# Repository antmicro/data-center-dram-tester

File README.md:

# Data Center RDIMM DDR4 Tester

Copyright (c) 2021-2023 [Antmicro](https://antmicro.com)

## Overview

This repository contains open hardware KiCad design files for an experimental platform built around the Xilinx Kintex-7 FPGA which can be used to interface with RDIMM DDR4 RAM modules used in data centers.

This hardware platform is used in Antmicro's and Google's [Rowhammer testing framework](https://github.com/antmicro/litex-rowhammer-tester) which can be used to perform (and potentially mitigate) Rowhammer attacks on DRAM memories. You can learn more about Rowhammer and our work towards mitigating it in a Google Open Source blog note [describing a related platform](https://opensource.googleblog.com/2021/11/Open%20source%20DDR%20controller%20framework%20for%20mitigating%20Rowhammer.html).
The usage instructions for this board are also provided in the [Rowhammer testing framework documentation](https://litex-rowhammer-tester.readthedocs.io/en/latest/). 

## Repository structure

The main repository directory contains KiCad PCB project files, a LICENSE and README.
The remaining files are stored in the following directories:

* `lib` - contains the component libraries
* `img` - contains graphics for this README

## Key Features

* Kintex-7 FPGA (XC7K160T-FFG676)
* DDR4 RDIMM connector with hotswap
* HDMI output connector
* Ethernet RJ45 connector with 1GbE transciever
* USB-C debug connector with FT4232HQ FTDI USB controller
* JTAG
* microSD card slot
* 16 MBytes S25FL128S QSPI FLASH memory
* S27KL0641 HyperRAM
* External 7-12V DC power input
* PoE++
* Power consumption monitoring
* 5 user LEDs
* Optional FMC HPC expansion connector

## Block diagram

## License

This project is published under the [Apache-2.0](LICENSE) license.

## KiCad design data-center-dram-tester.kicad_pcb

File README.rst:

=======================
Data Center DRAM Tester
=======================

Copyright (c) 2021-2022 `Antmicro <https://www.antmicro.com>`_

.. figure:: img/data-center-dram-tester.png

Overview
--------

This repository contains open hardware design files for an experimental platform built around Xilinx Kintex-7 FPGA.
The main purpose of this platform is to develop and customize RAM controllers supporting RDIMM DDR4 RAM modules used in data centers.

This hardware platform is supported by the `LiteX Rowhammer Tester <https://github.com/antmicro/litex-rowhammer-tester>`_ gateware. It can be used to investigate Rowhammer DRAM attacks. You can learn more about Rowhammer attacks from this blog `note <https://antmicro.com/blog/2021/08/open-source-ddr-test-framework-for-rowhammer/>`_.
The usage instructions for this board are also provided in the `LiteX Row Hammer Tester documentation <https://litex-rowhammer-tester.readthedocs.io/en/latest/>`_. 

The design files were prepared in KiCad.

Repository structure
--------------------
The main repository directory contains KiCad PCB project files, a LICENSE and README.
The remaining files are stored in the following directories:

* ``lib`` - contains the component libraries
* ``img`` - contains graphics for this README

Key Features
------------

* Kintex-7 FPGA - XC7K100T-FBG686
* DDR4 RDIMM connector
* HDMI output connector
* Ethernet RJ45 connector with 1GbE transciever
* Micro USB debug connector with FT4232HQ FTDI USB controller
* JTAG
* microSD card slot
* 16Mbytes S25FL128S QSPI FLASH memory
* S27KL0641 HyperRAM
* External 7-12V power input
* 5 user LEDs
* 4 user buttons

License
=======

`Apache-2.0 <LICENSE>`_

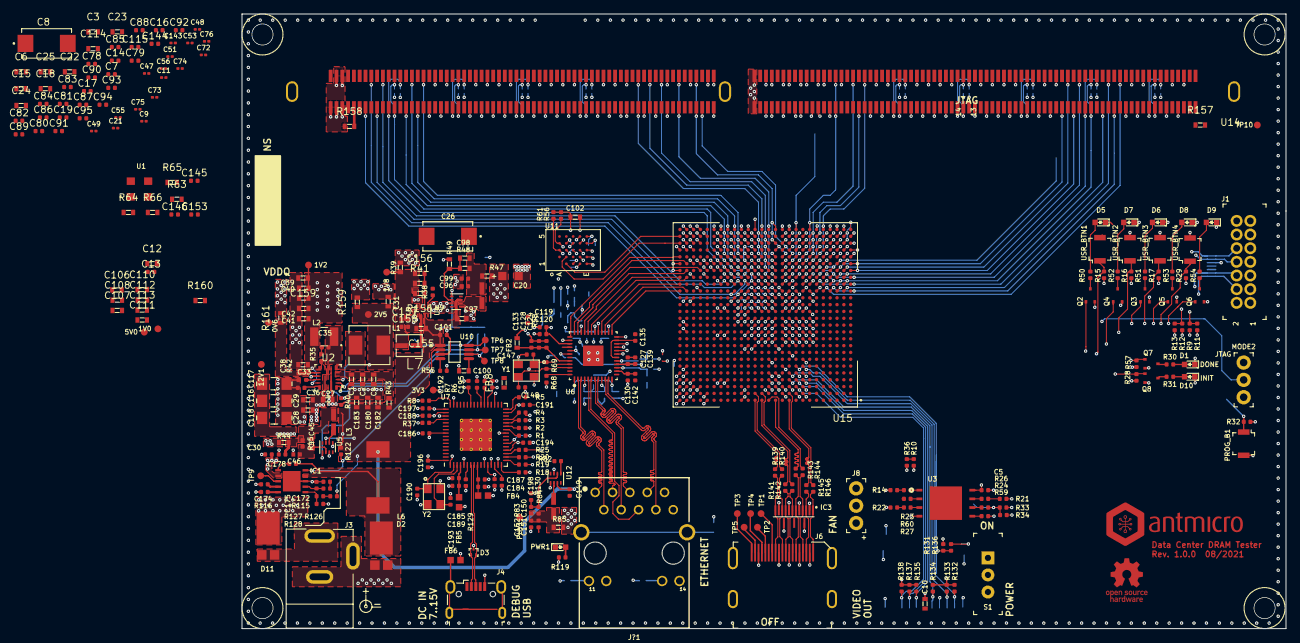
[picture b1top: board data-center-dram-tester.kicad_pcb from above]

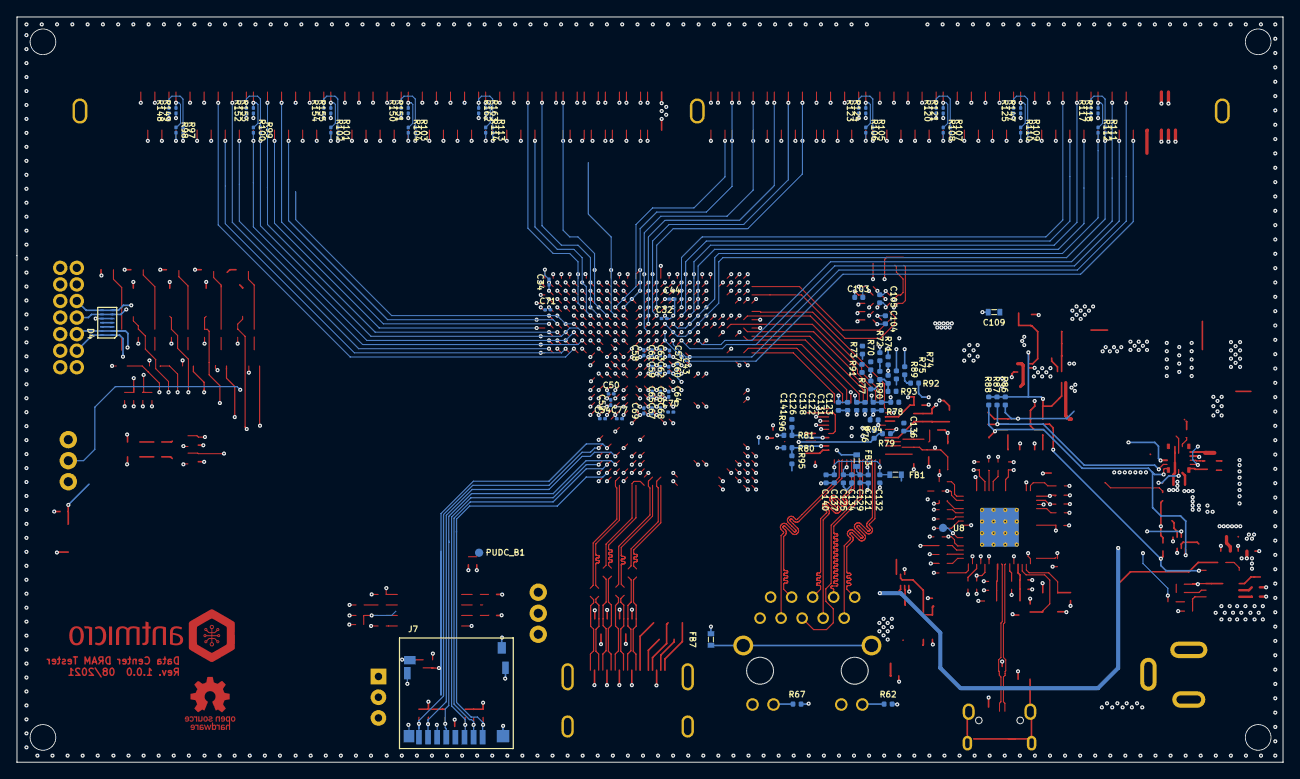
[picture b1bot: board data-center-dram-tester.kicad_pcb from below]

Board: 10 copper layers, 152.9 x 90.0 mm, 430 parts (109 on the bottom side), 375 nets.

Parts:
0V6, 1V0, 1V2, 1V8, 2V5, 3V3, 5V0, 12V1: TP_SMD1MM; Testpoint_smd_1mm
C1, C33, C155: C_10u_0603; 0603-cap
C2: C_100n_0603; 0603-cap
C3, C6, C12, C15, C18, C22, C23, C24, C25, C102, C114, C180, C182, C183: C_47u_0603; 0603-cap
C4, C10: C_1u_0603; 0603-cap
C5, C35, C101, C103, C104, C105, C145, C146, C153, C178, C184, C185, C186, C188, C191, C192, C194, C196, C197, C198: C_100n_0402_6V3; 0402-cap
C7, C14, C16, C17, C19, C78, C79, C80, C81, C82, C83, C84, C85, C86, C87, C88, C89, C90, C91, C92, C93, C94, C95, C115, C119, C121, C123, C124, C132, C144, C187, C189, C195: C_4u7_0402; 0402-cap
C8, C26: C_330u_KEMET_D; KEMET_D
C9, C11, C21, C32, C34, C43, C44, C47, C48, C49, C50, C51, C52, C53, C54, C55, C56, C57, C58, C59, C60, C61, C62, C63, C64, C65, C66, C67, C68, C69, C70, C71, C72, C73, C74, C75, C76, C77, C143: C_100n_0201; 0201-res
C13, C36, C120, C122, C125, C126, C127: C_470n_0402; 0402-cap
C20: C_100u_KEMET_A; KEMET_A
C27, C28, C29: C_10u_25V_0603; 0603-cap
C30: C_100n_0402_16V; 0402-cap
C31, C39, C40, C41, C42, C159: C_22u_0603; 0603-cap
C38, C46, C96, C99, C149, C151, C152, C157, C158: C_10u_0402; 0402-cap
C45, C98, C156: C_120p_0603; 0603-cap
C97: C_4u7_0603; 0603-cap
C100, C106, C107, C108, C109, C110, C111, C112, C113: C_10n_0603; 0603-cap
C116, C117, C118: C_47u_16V_1206; 1206-cap
C128: C_100n_0402; 0402-cap
C129, C130, C131, C133, C134, C135, C136, C137, C138, C139, C140, C141, C142, C174: C_10n_0402; 0402-cap
C147, C148: C_22p_0402; 0402-cap
C150: C_120p_0402; 0402-cap
C172: C_4n7_0402; 0402-cap
C175: C_47p_0402; 0402-cap
C190, C193: C_18p_0402; 0402-cap
D1, D5, D6, D7, D8, D9, D10: KP-1608CGCK; LED_0603
D2, D11: PDS760-13
D3: TPD2E009; SOT-3
D4: TPD6E05U06
FB1, FB2, FB3, FB7, FB8: BLM18PG121SN1D; 0603-res
FB4, FB5, FB6: BLM18AG601SN1D; 0603
IC1: TPS54561; WSON-10_4x4
IC3: TPD8S009DSMR; R-PDSO-N15
J1: 0878311420; PinHeader_2x7_P2mm_Drill1mm
J3: DC_SOCKET
J4: WE_629105150521; USB_Micro_B_Female_629105150521
J6: 685119134923; HDMI_A_Female_685119134923
J7: 1140084168; MicroSD_1140084168
J8: 61300311121; PinHeader_1x3_P2.54_Drill1.1mm
J?1: WE-RJ45_7499111121A; 7499111121A
L1: IHLP2020BZER4R7M01
L2: DFE322512F-R68M=P2; INDC3225X120N
L3, L4, L5, L7: IHLP1212AEERR47M11; IHLP-1212AE
L6: WE_7447798720
MODE2: 61300311121; PinHeader_1x3_P2.54_Drill1.1mm
N1: oshw_logo; oshw-logo
N2: antmicro_logo; antmicro-logo_scaled_20mm
PHY1: TP_SMD1MM; Testpoint_smd_1mm
PROG_B1: B3U-1000P; Switch_Tactile_SMD_B3U-1000P
PUDC_B1: test; Testpoint_smd_1mm
PWR1: KP-1608CGCK; LED_0603
Q2, Q3, Q4, Q5, Q6, Q7, Q8: BSS138APW; SC70-3
R1, R2, R3, R4, R5, R6, R7, R8, R18, R19, R20, R25, R37: R_22R_0402; 0402-res
R9, R11, R12, R13, R23, R24, R26, R27, R38, R42, R55, R58, R59, R60, R82, R139, R140, R141, R142, R143, R144, R145, R146: R_0R_0402; 0402-res
R10, R33, R34, R36: R_100R_0402; 0402-res
R14, R77, R89, R90, R91, R92, R93, R94, R95, R96: R_2k2_0402; 0402-res
R15, R16, R17, R21, R22, R28, R29, R32: R_4k7_0402; 0402-res
R30, R31, R50, R51, R52, R53, R54, R57, R119: R_330R_0402; 0402-res
R35: R_5R1_0402; 0402-res
R39, R43, R44, R47, R85, R157, R158, R159, R160, R161: R_0R_0603; 0603-res
R40, R83, R84, R122: R_100k_0402; 0402-res
R41: R_49R9_0603; 0603-res
R45: R_453k_0402; 0402-res
R46: R_100k_1%_0402; 0402
R48: R_66k5_0603; 0603-res
R49, R156: R_100k_0603; 0603-res
R56, R61, R86, R87, R88, R130: R_10k_0402; 0402-res
R62, R67, R136: R_220R_0402; 0402-res
R63, R64: R_120R_0603; 0603-res
R65, R66: R_1k_0603; 0603-res
R68: R_12k1_0402; 0402-res
R69: R_1M8_0402; 0402-res
R70, R71, R72, R73, R74, R75, R76, R79, R80, R81, R128: R_10k2_0402; 0402-res
R78: R_1k_0402; 0402-res
R97, R98, R99, R100, R101, R102, R103, R104, R105, R106, R107, R108, R109, R110, R111, R112, R113, R114, R117, R118, R120, R121, R123, R124, R125, R147, R148, R149, R150, R151, R152, R153, R154, R155, R162, R163: R_0R_0201; 0201-res
R115: R_16k9_0402; 0402-res
R116: R_243k_0402; 0402-res
R126: R_49R9_0402; 0402-res
R127: R_53k6_0402; 0402-res
R129: R_12k_0402; 0402-res
R131, R132, R133, R134, R135, R137, R138: R_20k_0402; 0402-res
S1: EG1218; Switch_Slide_11.6x4mm_EG1218
TP1, TP2, TP3, TP4, TP5, TP6, TP7, TP8, TP9, TP10: TP_SMD1MM; Testpoint_smd_1mm
U1: ASFLMB-100.000MHZ-XY-T
U2: TPS65295RJET
U3: S25FL128SAGNFI000
U4, U5, U9, U12: TPS62823DLCT; QFN-8_2x1mm
U6: KSZ9031RNXCA; QFN-48-Microchip-QFN77-48LD-PL-2
U7: FT4232HQ
U8: SRST; Testpoint_smd_1mm
U10: LM3881MME_NOPB; VSSOP8-Texas_Instruments-DGK0008A
U11: S27KL0641DABHI023; FBGA-24
U14: 2199155-1
U15: XC7K160T-FFG676; BGA676C100P26X26_2700X2700X254
USR_BTN1, USR_BTN2, USR_BTN3, USR_BTN4: B3U-1000P; Switch_Tactile_SMD_B3U-1000P
Y1: ABM8G-25.000MHZ-18-D2Y-T; KX-7
Y2: ABM8G-12.000MHZ-18-D2Y-T; KX-7

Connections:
1V0_SYS: C8.1, C14.1, C17.1, C20.1, C26.1, C50.1, C52.1, C54.1, C57.1, C58.1, C59.1, C60.1, C61.1, C62.1, C63.1, C64.1, C65.1, C66.1, C67.1, C68.1, C69.1, C70.1, C77.1, C144.1, R47.1, U15.J9, U15.K8, U15.K10, U15.K12, U15.K14, U15.L9, U15.L13, U15.L15, U15.M8, U15.M14, U15.N9, U15.N13, U15.N15, U15.P14, U15.R13, U15.R15, U15.T12, U15.T14, U15.U13, U15.U15
1V2_SYS: C119.1, C120.1, C122.1, C126.1, C130.1, C135.1, C138.1, C141.1, C142.1, FB2.2, FB3.2, R85.2, U6.14, U6.18, U6.23, U6.26, U6.30, U6.39
1V8_FT: C195.1, C196.1, C197.1, C198.1, FB8.1, U7.12, U7.37, U7.49, U7.64
1V8_SYS: C7.1, C9.1, C11.1, C16.1, C19.1, C22.1, C25.1, C47.1, C48.1, C49.1, C51.1, C53.1, C55.1, C56.1, C114.1, C115.1, FB8.2, R39.2, U15.E8, U15.L11, U15.M10, U15.M12, U15.P10, U15.T10, U15.U11
3V3_SYS: C3.1, C5.1, C6.1, C10.1, C12.1, C13.1, C15.1, C18.1, C78.1, C79.1, C80.1, C81.1, C82.1, C83.1, C84.1, C85.1, C86.1, C87.1, C88.1, C89.1, C90.1, C91.1, C92.1, C93.1, C94.1, C95.1, C102.1, C103.1, C104.1, C105.1, C123.1, C127.1, C131.1, C136.1, C139.1, C145.1, C186.1, C188.1, C191.1, C192.1, C194.1, D1.1, D5.1, D6.1, D7.1, D8.1, D9.1, D10.1, FB1.1, FB4.1, FB5.1, IC3.13, IC3.15, J1.2, J7.4, MODE2.3, PWR1.1, R9.2, R10.1, R12.2, R14.2, R15.1, R16.1, R17.1, R21.1, R22.1, R28.1, R29.1, R32.1, R33.1, R44.1, R56.1, R57.1, R58.1, R61.1, R62.2, R67.2, R70.2, R71.2, R72.2, R73.2, R74.2, R75.2, R76.2, R78.2, R79.2, R80.2, R81.2, R130.1, R131.1, R132.1, R133.1, R134.1, R135.1, R137.1, R138.1, U1.1, U1.4, U3.8, U6.16, U6.34, U6.40, U7.20, U7.31, U7.42, U7.50, U7.56, U11.B4, U11.D1, U11.E4, U15.A11, U15.A21, U15.AA21, U15.AC25, U15.AD22, U15.AF26, U15.B8, U15.C25, U15.D12, U15.D22, U15.E9, U15.F26, U15.G13, U15.G23, U15.H10, U15.L7, U15.L21, U15.T6, U15.U23, U15.V20, U15.Y24
5V0_SYS: C2.1, C4.1, R40.2, R43.2, U2.13, U2.14
/Ethernet/AVDDH: C132.1, C137.1, C140.1, FB1.2, U6.1, U6.12
/Ethernet/AVDDL: C121.1, C125.1, C129.1, C134.1, FB3.1, U6.4, U6.9
/Ethernet/AVDDL_PLL: C124.1, C128.1, C133.1, FB2.1, U6.44
/Ethernet/ETH1_N: J?1.2, U6.3
/Ethernet/ETH1_P: J?1.1, U6.2
/Ethernet/ETH2_N: J?1.6, U6.6
/Ethernet/ETH2_P: J?1.3, U6.5
/Ethernet/ETH3_N: J?1.5, U6.8
/Ethernet/ETH3_P: J?1.4, U6.7
/Ethernet/ETH4_N: J?1.8, U6.11
/Ethernet/ETH4_P: J?1.7, U6.10
/Supply/SYS_EN: IC1.3, S1.2, TP9.1
/Supply/VCC_AUX_EN: R38.2, R87.2, TP7.1, U2.11, U10.7
/Supply/VCC_INT_EN: R86.2, TP6.1, U9.1, U10.8
/Supply/VCC_IO_EN: R82.2, R88.2, TP8.1, U2.10, U5.1, U10.6
/Supply/VTTREF: C36.1, U2.6
A0: U14.79, U15.V12
A1: U14.72, U15.AC11
A2: U14.216, U15.AD11
A3: U14.71, U15.AD10
A4: U14.214, U15.AC9
A5: U14.213, U15.AD9
A6: U14.69, U15.AB9
A7: U14.211, U15.AF7
A8: U14.68, U15.AE8
A9: U14.66, U15.AE7
A10\AP: U14.225, U15.Y12
A11: U14.210, U15.AC7
A12\~BC: U14.65, U15.AB7
A13: U14.232, U15.AD13
A17: U14.234, U15.AC13
AUX_JTAG_TCK: R1.2, U15.C24
AUX_JTAG_TDI: R2.2, U15.D24
AUX_JTAG_TDO: R3.2, U15.C26
AUX_JTAG_TMS: R4.2, U15.D25
BA0: U14.81, U15.AB11
BA1: U14.224, U15.AB10
BG0: U14.63, U15.AA9
BG1: U14.207, U15.AF9
CB0: U14.49, U15.AF3
CB1: U14.194, U15.AE5
CB2: U14.56, U15.AD6
CB3: U14.201, U15.AC6
CB4: U14.47, U15.AF2
CB5: U14.192, U15.AE3
CB6: U14.54, U15.AE6
CB7: U14.199, U15.AD5
CCLK: R24.2, R33.2, R34.1, U15.C8
CFGBVS: R58.2, U15.P7
CK0_C: U14.75, U15.AF12
CK0_T: U14.74, U15.AE12
CK1_C: U14.219, U15.AB12
CK1_T: U14.218, U15.AC12
CKE0: U14.60, U15.AA8
CKE1\NC: U14.203, U15.AA7
C_TMDS_CLK_N: IC3.12, J6.12, R139.2
C_TMDS_CLK_P: IC3.10, J6.10, R140.2
C_TMDS_D0_N: IC3.9, J6.9, R141.2
C_TMDS_D0_P: IC3.7, J6.7, R142.2
C_TMDS_D1_N: IC3.6, J6.6, R143.2
C_TMDS_D1_P: IC3.4, J6.4, R144.2
C_TMDS_D2_N: IC3.3, J6.3, R145.2
C_TMDS_D2_P: IC3.1, J6.1, R146.2
DBG_USB_N: D3.1, J4.2, U7.7
DBG_USB_P: D3.2, J4.3, U7.8
DONE: Q7.1, R57.2, U15.J7
DQ0: U14.5, U15.W11
DQ1: U14.150, U15.Y11
DQ2: U14.12, U15.V7
DQ3: U14.157, U15.Y7
DQ4: U14.3, U15.V11
DQ5: U14.148, U15.V9
DQ6: U14.10, U15.V8
DQ7: U14.155, U15.W8
DQ8: U14.16, U15.U2
DQ9: U14.161, U15.V6
DQ10: U14.23, U15.Y2
DQ11: U14.168, U15.Y3
DQ12: U14.14, U15.U5
DQ13: U14.159, U15.U4
DQ14: U14.21, U15.W3
DQ15: U14.166, U15.Y1
DQ16: U14.27, U15.AA2
DQ17: U14.172, U15.AB2
DQ18: U14.34, U15.AE1
DQ19: U14.179, U15.AE2
DQ20: U14.25, U15.V2
DQ21: U14.170, U15.W1
DQ22: U14.32, U15.AD1
DQ23: U14.177, U15.AC2
DQ24: U14.38, U15.W4
DQ25: U14.183, U15.AA3
DQ26: U14.45, U15.AD3
DQ27: U14.190, U15.AC4
DQ28: U14.36, U15.V3
DQ29: U14.181, U15.V4
DQ30: U14.43, U15.AB4
DQ31: U14.188, U15.AC3
DQ32: U14.97, U15.AC16
DQ33: U14.242, U15.AC17
DQ34: U14.104, U15.AB16
DQ35: U14.249, U15.AA19
DQ36: U14.95, U15.AB15
DQ37: U14.240, U15.AD16
DQ38: U14.102, U15.AC18
DQ39: U14.247, U15.AC19
DQ40: U14.108, U15.AF17
DQ41: U14.253, U15.AE17
DQ42: U14.115, U15.AF20
DQ43: U14.260, U15.AD19
DQ44: U14.106, U15.AE15
DQ45: U14.251, U15.AE16
DQ46: U14.113, U15.AF19
DQ47: U14.258, U15.AD18
DQ48: U14.119, U15.Y18
DQ49: U14.264, U15.Y17
DQ50: U14.126, U15.W14
DQ51: U14.271, U15.V14
DQ52: U14.117, U15.AA20
DQ53: U14.262, U15.AA15
DQ54: U14.124, U15.V18
DQ55: U14.269, U15.W16
DQ56: U14.130, U15.AA18
DQ57: U14.275, U15.AB19
DQ58: U14.137, U15.V16
DQ59: U14.282, U15.W15
DQ60: U14.128, U15.AB17
DQ61: U14.273, U15.AA17
DQ62: U14.135, U15.V19
DQ63: U14.280, U15.V17
DQS0_C: R98.2, U14.152, U15.W9
DQS0_T: R97.2, U14.153, U15.W10
DQS1_C: R100.2, U14.163, U15.W5
DQS1_T: R99.2, U14.164, U15.W6
DQS2_C: R102.2, U14.174, U15.AC1
DQS2_T: R101.2, U14.175, U15.AB1
DQS3_C: R104.2, U14.185, U15.AB5
DQS3_T: R103.2, U14.186, U15.AA5
DQS4_C: R106.2, U14.244, U15.AE20
DQS4_T: R105.2, U14.245, U15.AD20
DQS5_C: R108.2, U14.255, U15.AF18
DQS5_T: R107.2, U14.256, U15.AE18
DQS6_C: R110.2, U14.266, U15.W19
DQS6_T: R109.2, U14.267, U15.W18
DQS7_C: R112.2, U14.277, U15.Y16
DQS7_T: R111.2, U14.278, U15.Y15
DQS8_C: R114.2, U14.196, U15.AF4
DQS8_T: R113.2, U14.197, U15.AF5
DQS9_C: R98.1, R149.2, U14.8
DQS9_T: R97.1, R148.2, U14.7
DQS10_C: R100.1, R153.2, U14.19
DQS10_T: R99.1, R152.2, U14.18
DQS11_C: R102.1, R155.2, U14.30
DQS11_T: R101.1, R154.2, U14.29
DQS12_C: R104.1, R151.2, U14.41
DQS12_T: R103.1, R150.2, U14.40
DQS13_C: R106.1, R124.2, U14.100
DQS13_T: R105.1, R123.2, U14.99
DQS14_C: R108.1, R121.2, U14.111
DQS14_T: R107.1, R120.2, U14.110
DQS15_C: R110.1, R147.2, U14.122
DQS15_T: R109.1, R125.2, U14.121
DQS16_C: R112.1, R118.2, U14.133
DQS16_T: R111.1, R117.2, U14.132
DQS17_C: R114.1, R163.1, U14.52
DQS17_T: R113.1, R162.1, U14.51
ETH_INT_N: U6.38, U15.Y20
ETH_MDC: U6.36, U15.AA25
ETH_MDIO: R78.1, U6.37, U15.AB26
ETH_REF_CLK: R76.1, R94.1, U6.41, U15.AA23
ETH_RSTN: R79.1, U6.42, U15.AA22
ETH_RXD0: R70.1, R77.1, U6.32, U15.W26
ETH_RXD1: R71.1, R89.1, U6.31, U15.W25
ETH_RXD2: R72.1, R90.1, U6.28, U15.V26
ETH_RXD3: R73.1, R91.1, U6.27, U15.U25
ETH_RX_CLK: R75.1, R93.1, U6.35, U15.Y23
ETH_RX_DV: R74.1, R92.1, U6.33, U15.Y25
ETH_TXD0: U6.19, U15.W24
ETH_TXD1: U6.20, U15.Y26
ETH_TXD2: U6.21, U15.Y22
ETH_TXD3: U6.22, U15.Y21
ETH_TX_CLK: U6.24, U15.AA24
ETH_TX_EN: U6.25, U15.U26
FCS_B: R14.1, R23.2, U15.C23
GND: C1.2, C2.2, C3.2, C4.2, C5.2, C6.2, C7.2, C8.2, C9.2, C10.2, C11.2, C12.2, C13.2, C14.2, C15.2, C16.2, C17.2, C18.2, C19.2, C20.2, C21.2, C22.2, C23.2, C24.2, C25.2, C26.2, C27.2, C28.2, C29.2, C30.2, C31.2, C32.2, C33.2, C34.2, C36.2, C38.2, C39.2, C40.2, C41.2, C42.2, C43.2, C44.2, C46.2, C47.2, C48.2, C49.2, C50.2, C51.2, C52.2, C53.2, C54.2, C55.2, C56.2, C57.2, C58.2, C59.2, C60.2, C61.2, C62.2, C63.2, C64.2, C65.2, C66.2, C67.2, C68.2, C69.2, C70.2, C71.2, C72.2, C73.2, C74.2, C75.2, C76.2, C77.2, C78.2, C79.2, C80.2, C81.2, C82.2, C83.2, C84.2, C85.2, C86.2, C87.2, C88.2, C89.2, C90.2, C91.2, C92.2, C93.2, C94.2, C95.2, C96.2, C97.2, C99.2, C100.1, C101.2, C102.2, C103.2, C104.2, C105.2, C106.2, C107.2, C108.2, C109.2, C110.2, C111.2, C112.2, C113.2, C114.2, C115.2, C116.2, C117.2, C118.2, C119.2, C120.2, C121.2, C122.2, C123.2, C124.2, C125.2, C126.2, C127.2, C128.2, C129.2, C130.2, C131.2, C132.2, C133.2, C134.2, C135.2, C136.2, C137.2, C138.2, C139.2, C140.2, C141.2, C142.2, C143.2, C144.2, C145.2, C146.2, C147.2, C148.2, C149.2, C151.2, C152.2, C153.2, C155.2, C157.2, C158.2, C159.2, C172.2, C174.2, C175.2, C180.2, C182.2, C183.2, C184.2, C185.2, C186.2, C187.2, C188.2, C189.2, C190.2, C191.2, C192.2, C193.2, C194.2, C195.2, C196.2, C197.2, C198.2, D2.A, D3.3, D4.5, D4.10, FB6.1, FB7.2, IC1.8, IC1.11, IC3.2, IC3.5, IC3.8, IC3.11, J1.1, J1.3, J1.5, J1.7, J1.9, J1.11, J1.13, J3.2, J3.3, J4.5, J6.2, J6.5, J6.8, J6.11, J6.17, J6.SH, J7.6, J7.10, J7.~, J8.3, J?1.10, MODE2.1, PROG_B1.2, Q2.2, Q3.2, Q4.2, Q5.2, Q6.2, Q7.2, Q8.2, R11.2, R13.2, R34.2, R36.2, R46.2, R49.2, R55.2, R64.2, R66.2, R68.1, R77.2, R84.2, R89.2, R90.2, R91.2, R92.2, R93.2, R94.2, R95.2, R96.2, R116.1, R119.2, R128.2, R129.1, R156.2, S1.3, U1.2, U2.3, U2.9, U2.16, U3.4, U4.3, U4.5, U5.3, U5.5, U6.29, U6.49, U7.1, U7.5, U7.11, U7.13, U7.15, U7.25, U7.35, U7.47, U7.51, U7.65, U9.3, U9.5, U10.3, U11.B3, U11.C1, U11.E5, U12.3, U12.5, U14.2, U14.4, U14.6, U14.9, U14.11, U14.13, U14.15, U14.17, U14.20, U14.22, U14.24, U14.26, U14.28, U14.31, U14.33, U14.35, U14.37, U14.39, U14.42, U14.44, U14.46, U14.48, U14.50, U14.53, U14.55, U14.57, U14.94, U14.96, U14.98, U14.101, U14.103, U14.105, U14.107, U14.109, U14.112, U14.114, U14.116, U14.118, U14.120, U14.123, U14.125, U14.127, U14.129, U14.131, U14.134, U14.136, U14.138, U14.147, U14.149, U14.151, U14.154, U14.156, U14.158, U14.160, U14.162, U14.165, U14.167, U14.169, U14.171, U14.173, U14.176, U14.178, U14.180, U14.182, U14.184, U14.187, U14.189, U14.191, U14.193, U14.195, U14.198, U14.200, U14.202, U14.204, U14.206, U14.209, U14.212, U14.215, U14.217, U14.220, U14.239, U14.241, U14.243, U14.246, U14.248, U14.250, U14.252, U14.254, U14.257, U14.259, U14.261, U14.263, U14.265, U14.268, U14.270, U14.272, U14.274, U14.276, U14.279, U14.281, U14.283, U15.A1, U15.A2, U15.A5, U15.A6, U15.A7, U15.A16, U15.A26, U15.AA6, U15.AA16, U15.AA26, U15.AB3, U15.AB13, U15.AB23, U15.AC10, U15.AC20, U15.AD7, U15.AD17, U15.AE4, U15.AE14, U15.AE24, U15.AF1, U15.AF11, U15.AF21, U15.B4, U15.B7, U15.B13, U15.B23, U15.C1, U15.C5, U15.C7, U15.C10, U15.C20, U15.D4, U15.D7, U15.D17, U15.E1, U15.E2, U15.E5, U15.E7, U15.E14, U15.E24, U15.F3, U15.F4, U15.F7, U15.F11, U15.F21, U15.G1, U15.G5, U15.G8, U15.G18, U15.H4, U15.H7, U15.H15, U15.H25, U15.J1, U15.J2, U15.J5, U15.J12, U15.J22, U15.K3, U15.K4, U15.K7, U15.K9, U15.K11, U15.K13, U15.K19, U15.L1, U15.L5, U15.L10, U15.L12, U15.L14, U15.L16, U15.L26, U15.M4, U15.M7, U15.M9, U15.M11, U15.M13, U15.M15, U15.M23, U15.N1, U15.N2, U15.N5, U15.N7, U15.N10, U15.N11, U15.N12, U15.N14, U15.N20, U15.P3, U15.P4, U15.P9, U15.P11, U15.P12, U15.P13, U15.P15, U15.P17, U15.R1, U15.R2, U15.R5, U15.R8, U15.R10, U15.R11, U15.R12, U15.R14, U15.R24, U15.T1, U15.T3, U15.T4, U15.T9, U15.T11, U15.T13, U15.T15, U15.T21, U15.U8, U15.U10, U15.U12, U15.U14, U15.U18, U15.V5, U15.V15, U15.V25, U15.W2, U15.W12, U15.W22, U15.Y9, U15.Y19, USR_BTN1.2, USR_BTN2.2, USR_BTN3.2, USR_BTN4.2, Y1.2, Y1.4, Y2.2, Y2.4
HR_CKN: U11.B1, U15.AE26
HR_CKP: U11.B2, U15.AD26
HR_CS: R61.2, U11.A3, U15.AC26
HR_DQ0: U11.D3, U15.AE23
HR_DQ1: U11.D2, U15.AD25
HR_DQ2: U11.C4, U15.AF24
HR_DQ3: U11.D4, U15.AE22
HR_DQ4: U11.D5, U15.AF23
HR_DQ5: U11.E3, U15.AF25
HR_DQ6: U11.E2, U15.AE25
HR_DQ7: U11.E1, U15.AD24
HR_RST: R56.2, U11.A4, U15.AC24
HR_RW: U11.C3, U15.AD23
INIT_B: Q8.1, R28.2, U15.G7
LED_LINK: J?1.12, R81.1, R96.1, U6.17
LED_SPD: J?1.14, R80.1, R95.1, U6.15
MODE0: R9.1, R11.1, U15.T5
MODE1: R12.1, R13.1, U15.T2
MODE2: MODE2.2, U15.P5
NC: R157.1, TP10.1, U14.1, U14.145
NC\C2: U14.235, U15.AD14
unnamed: C35.1, L2.1, U2.17
unnamed: C35.2, R35.2
unnamed: C45.2, R45.2, R46.1, U5.2
unnamed: C98.2, R48.2, R49.1, U9.2
unnamed: C100.2, U10.5
unnamed: C147.1, R69.1, U6.45, Y1.1
unnamed: C148.1, R69.2, U6.46, Y1.3
unnamed: C150.2, R83.2, R84.1, U12.2
unnamed: C156.2, R41.2, R156.1, U4.2
unnamed: C172.1, R115.2
unnamed: C174.1, IC1.4
unnamed: C175.1, IC1.7, R115.1
unnamed: C178.1, D2.C, IC1.9, L6.1
unnamed: C178.2, IC1.1
unnamed: C184.1, C187.1, FB4.2, U7.9
unnamed: C185.1, C189.1, FB5.2, U7.4
unnamed: C190.1, U7.2, Y2.1
unnamed: C193.1, U7.3, Y2.3
unnamed: D1.2, R30.1
unnamed: D5.2, R50.1
unnamed: D6.2, R51.1
unnamed: D7.2, R52.1
unnamed: D8.2, R53.1
unnamed: D9.2, R54.1
unnamed: D10.2, R31.1
unnamed: D11.A, J3.1
unnamed: FB6.2, J4.6
unnamed: FB7.1, J?1.Z1, J?1.Z2
unnamed: IC1.5, R116.2
unnamed: IC1.6, R127.2, R128.1
unnamed: J6.13, TP1.1
unnamed: J6.15, TP2.1
unnamed: J6.16, TP4.1
unnamed: J6.18, TP5.1
unnamed: J6.19, TP3.1
unnamed: J7.9, R136.2
unnamed: J?1.11, R62.1
unnamed: J?1.13, R67.1
unnamed: L1.1, U2.15
unnamed: L3.1, U5.6
unnamed: L4.1, U9.6
unnamed: L5.1, U12.6
unnamed: L7.1, U4.6
unnamed: PWR1.2, R119.1
unnamed: Q2.3, R50.2
unnamed: Q3.3, R51.2
unnamed: Q4.3, R52.2
unnamed: Q5.3, R53.2
unnamed: Q6.3, R54.2
unnamed: Q7.3, R30.2
unnamed: Q8.3, R31.2
unnamed: R1.1, U7.26
unnamed: R2.1, U7.27
unnamed: R3.1, U7.28
unnamed: R4.1, U7.29
unnamed: R5.1, U7.32
unnamed: R6.1, U7.38
unnamed: R7.1, U7.39
unnamed: R8.1, U7.48
unnamed: R18.1, U7.16
unnamed: R19.1, U7.17
unnamed: R20.1, U7.18
unnamed: R23.1, U3.1
unnamed: R24.1, U3.6
unnamed: R25.1, U7.19
unnamed: R26.1, U3.7
unnamed: R27.1, U3.3
unnamed: R35.1, U2.18
unnamed: R37.1, U7.52
unnamed: R38.1, U4.1
unnamed: R40.1, U2.8
unnamed: R42.1, U2.4
unnamed: R55.1, U10.4
unnamed: R59.1, U3.5
unnamed: R60.1, U3.2
unnamed: R68.2, U6.48
unnamed: R82.1, U12.1
unnamed: R117.1, U15.M25
unnamed: R118.1, U15.L25
unnamed: R120.1, U15.P19
unnamed: R121.1, U15.P20
unnamed: R123.1, U15.T24
unnamed: R124.1, U15.T25
unnamed: R125.1, U15.R16
unnamed: R126.2, R127.1
unnamed: R129.2, U7.6
unnamed: R130.2, U7.14
unnamed: R147.1, U15.R17
unnamed: R148.1, U15.B17
unnamed: R149.1, U15.A17
unnamed: R150.1, U15.J15
unnamed: R151.1, U15.J16
unnamed: R152.1, U15.D19
unnamed: R153.1, U15.D20
unnamed: R154.1, U15.L19
unnamed: R155.1, U15.L20
unnamed: R162.2, U15.AC8
unnamed: R163.2, U15.AD8
unnamed: U7.22, U8.1
ODT0: U14.87, U15.Y13
ODT1\NC: U14.91, U15.AB14
PARITY: U14.222, U15.AE13
PROGRAM_B: PROG_B1.1, R32.2, U15.P6
PUDC_B: PUDC_B1.1, R10.2, R36.1, U15.B25
QSPI_DQ0: R59.2, U15.B24
QSPI_DQ1: R60.2, U15.A25
QSPI_DQ2: R22.2, R27.2, U15.B22
QSPI_DQ3: R21.2, R26.2, U15.A22
SA2: U14.238, U15.V13
SD_CD: R131.2, R136.1, U15.F9
SD_CLK: J7.5, R134.2, U15.D10
SD_CMD: J7.3, R135.2, U15.D8
SD_DAT0: J7.7, R133.2, U15.E10
SD_DAT1: J7.8, R132.2, U15.F8
SD_DAT2: J7.1, R138.2, U15.C9
SD_DAT3: J7.2, R137.2, U15.D9
SYS_ON: IC1.10, R122.2, U10.2
TCK_JTAG: D4.13, J1.6, R18.2, U15.L8
TDI_JTAG: D4.8, J1.10, R19.2, U15.R6
TDO_JTAG: D4.9, J1.8, R20.2, U15.R7
TMDS_CLK_N: R139.1, U15.A15
TMDS_CLK_P: R140.1, U15.B15
TMDS_D0_N: R141.1, U15.A14
TMDS_D0_P: R142.1, U15.B14
TMDS_D1_N: R143.1, U15.A12
TMDS_D1_P: R144.1, U15.A13
TMDS_D2_N: R145.1, U15.A10
TMDS_D2_P: R146.1, U15.B10
TMS_JTAG: D4.14, J1.4, R25.2, U15.N8
UART0_RX: R6.2, U15.F25
UART0_TX: R7.2, U15.E26
UART1_RX: R8.2, U15.E25
UART1_TX: R37.2, U15.D26
USR_BTN1: R15.2, USR_BTN1.1
USR_BTN2: R16.2, USR_BTN2.1
USR_BTN3: R17.2, USR_BTN3.1
USR_BTN4: R29.2, USR_BTN4.1
VCC0V6: 0V6.1, C38.1, R42.2, R161.1, U2.2
VCC1V0: 1V0.1, C96.1, C98.1, C99.1, L4.2, R47.2, R48.1
VCC1V2: C150.1, C151.1, C152.1, L5.2, PHY1.1, R83.1, R85.1
VCC1V8: 1V8.1, C156.1, C157.1, C158.1, L7.2, R39.1, R41.1
VCC2V5: 2V5.1, C31.1, L1.2, R159.1, U2.12
VCC3V3: 3V3.1, C45.1, C46.1, L3.2, R44.2, R45.1
VCC5V0: 5V0.1, C97.1, C101.1, C149.1, C155.1, C180.1, C182.1, C183.1, J8.1, L6.2, R43.1, R86.1, R87.1, R88.1, R122.1, R126.1, U4.7, U5.7, U9.7, U10.1, U12.7
VDD1V2: 1V2.1, C33.1, C39.1, C40.1, C41.1, C42.1, C159.1, L2.2, R160.1, U2.1, U2.5
VDDQ: C21.1, C23.1, C24.1, C32.1, C34.1, C43.1, C44.1, C71.1, C72.1, C73.1, C74.1, C75.1, C76.1, C106.1, C107.1, C108.1, C109.1, C143.1, R63.2, R65.1, R160.2, U14.59, U14.61, U14.64, U14.67, U14.70, U14.73, U14.76, U14.80, U14.83, U14.85, U14.88, U14.90, U14.92, U14.223, U14.226, U14.229, U14.231, U14.233, U14.236, U15.AA1, U15.AA11, U15.AB8, U15.AB18, U15.AC5, U15.AC15, U15.AD2, U15.AD12, U15.AE9, U15.AE19, U15.AF6, U15.AF16, U15.B18, U15.E19, U15.F16, U15.H20, U15.J17, U15.K24, U15.M18, U15.N25, U15.P22, U15.R19, U15.T16, U15.T26, U15.U3, U15.V10, U15.W7, U15.W17, U15.Y4, U15.Y14
VDDSPD: R158.2, U14.284
VIN: 12V1.1, C27.1, C28.1, C29.1, C30.1, C116.1, C117.1, C118.1, D11.C, IC1.2, R157.2, U2.7
VPP: C110.1, C111.1, C112.1, C113.1, R158.1, R159.2, U14.142, U14.143, U14.286, U14.287, U14.288
VREF_34: C146.1, C153.1, R65.2, R66.1
VTT: R161.2, U14.77, U14.221
~ACT: U14.62, U15.Y8
~ALERT: U14.208, U15.AE10
~CAS~\A15: U14.86, U15.AF13
~CS0: U14.84, U15.W13
~CS1~\NC: U14.89, U15.AA14
~CS2~\C0: U14.93, U15.AC14
~CS3~\C1,NC: U14.237, U15.AF15
~EVENT: U14.78, U15.AF14
~RAS~\A16: U14.82, U15.AA12
~RESET: U14.58, U15.AB6
~SAVE: U14.230, U15.Y10
~WE~\A14: U14.228, U15.AA13

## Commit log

2021-06-24 Initial commit - add design files from LPDDR4 board
2021-08-19 Add DQS[9:17] routing through 0R
2021-08-19 Clean up schematic
2021-08-19 Remap address pins to release DQS pair
2021-08-19 Change board outline, import DIMM connector and FPGA to PCB
2021-08-19 Component placement draft
2021-08-19 Connect QSPI (fix), GPIOs, JTAG, HR, UART
2021-08-19 Add BGA fanout-WIP
2021-08-19 Clean up schematics-remove LPDDR4 reference schematic
2021-08-19 Add DDR4 signal labels to the schematic
2021-08-19 Reroute address pins into bank 33
2021-08-19 ADD DDR4 connection to FPGA and signals routing - WIP
2021-08-19 Add DD4 pinout, connect ethernet, QSPI, TMDS, SDIO
2021-08-19 Clean up schematics
2021-08-19 Change labels to global labels
2021-08-19 Add DDR4 fanout
2021-08-19 Connect DDR4 signals to FPGA - WIP
2021-08-19 Add LICENSE
2021-08-19 Add decoupling capacitors
2021-08-19 Add ddr4 adress pin routing
2021-08-19 Clean up main schematic
2021-08-19 Add local libraries
2021-08-19 Update title blocks on the schematics
2021-08-19 Clean up the schematics
2021-08-19 Add DQS[9:17] redundant connection
2021-08-19 Update layer stack table
2021-08-19 Add hyper ram routing
2021-08-19 Add HDMI routing
2021-08-19 Add ethernet routing
2021-08-19 Update naming convention
2021-08-19 Update 3DVis
2021-08-19 Add README
2021-08-19 Add PDF schematic
2021-08-19 Remove sch
2021-08-19 Fix PDF schematic
2021-08-20 Scale main schematic elements
2021-08-21 Update DDR4 PIMC
2021-08-21 Add 1V8 power supply
2021-08-21 Update power supply labels
2021-08-23 Mark DNP resistors
2021-08-23 Update pinout
    Add testpad and DNP 0R at 12V dedicated for NVRDIMM
2021-08-23 Update power sequencing
2021-08-23 Add Power Supply component placement - WIP
2021-08-23 Placing capacitors under FPGA - WIP
2021-08-24 Add power supply layout - WIP
2021-08-24 Add debug USB layout
2021-08-25 Add power planes
2021-08-25 Add JTAG layout
2021-08-25 Add PHY layout
2021-08-25 Add layout of a miscellaneous signals
2021-08-26 Connect LEDs and buttons
2021-08-26 Add 1V8 and VIN power planes
2021-08-26 Add vias under FPGA
2021-08-26 Update the PDF with schematics
2021-08-31 Place capacitors under the FPGA
2021-08-31 Connect VRN VRP and GCLK100
2021-08-31 Tune the length of the DDR4 traces
2021-08-31 Clean up designators
2021-09-28 Add SPD connection to the schematic
2021-09-29 Add SPD layout
2021-09-29 Solve DRC errors and clean up the designators
2021-09-29 Replace 0R power supply resistors with fuses
2021-10-20 Fix via fence
2021-10-20 Fix In7 DQ plane reference
2021-10-21 Fix CKO and CK1 signalls
2021-10-21 Add return vias near the DIMM connector
2021-10-21 Add labels to DQS[9:17] and route them as differential pairs
2021-10-27 Add DIMM power supplies decoupling
2021-10-29 Re-design connection of DQS[9:17] selectors
2021-10-29 Edit 1V8 power plane on VCC2
2021-10-29 Bump revision to 1.0.1
2021-10-29 Update library
2021-10-29 Remove redundant files
2021-11-02 Ignore generated artifacts
2021-11-02 Gerbers used for NCAB quotation
2021-11-04 Update PCBWay stackup in the table
2021-11-04 Increase the number of layers to 12
2021-11-04 Reduce the blind via pairs by one
2021-11-17 Adjust traces width to PCBWay stackup
2021-11-19 Bump rev to 1.0.2
2021-12-16 Update local libraries
2021-12-16 Stop ignoring img
2021-12-16 Remove redundant models, remove data from revision marking
2021-12-16 Update 3D Vis
2022-01-21 Add photo
2022-03-03 Connect RDIMM pins 206,209,212,215,217,220 to VDDQ instead of GND
2022-03-03 Bump the revision to 1.1.0, Update layout, DRC-clean
2022-03-03 Add logotypes
2022-03-03 Update schematic pdf
2022-03-04 Reconnect SPD I2C
2022-03-04 Fix VDDQ capacitors
2022-03-04 Add missing 3D models
2022-03-14 Replace R41 with 200k #32496
2022-03-14 Add flashing mode selector legend on silkscreen
2022-03-18 Replace R159 and R161 with ferrite beads #32498
2022-04-14 Update PCB with changes from schematic
2022-04-14 Change TPS62823DLCT to MP2162BGQH. Apply changes to PCB
2022-04-15 README: add links to external resources/docs
2022-04-15 Bump dates for copyrights
2022-05-17 Update the README to md, review.
2022-05-17 Fix image
2022-05-25 Add Badge
2022-05-26 Notes added by 'git notes add'
2022-05-27 Scale image
2022-06-30 Fix FPGA MPN mentioned in README
2022-07-20 Change DC/DC into DIODES/AP62301WU-7
2022-07-20 Finalise schematic changes
2022-07-20 Update PCB layout
2022-07-20 Finalise DC-DC migration on PCB
2022-07-20 Convert readme to .md, resize photo, add badge
2022-07-20 Bump revision to 1.1.1
2022-07-20 Minor silkscreen changes, add date
2022-07-20 Adjust meanders adjusted to PCB manufacturer EQ recommendation
2022-07-20 Meander modification checked with the script, prototype order W200350ASK125 (Gerbers 2022-06-15)
2022-07-20 Increased RGMII meander spacing on TOP layer, PCB order W200350ASK125 (Gerbers 2022-06-17)
2022-08-12 Migrate the project to KiCad 6, fix U8 EN-GND cross, bumped revision to 1.1.2
2022-09-06 Manufacturability improvements, revision bump to 1.1.3
2022-09-06 Finish migration to KiCad6. Cleanup legacy files. Remove local paths
2022-09-06 Add PoE circuitry, reorganize Ethernet sheet
2022-09-06 Fix finish layout of the PoE, fix Ethernet traces
2022-09-06 Add PoE circuitry to PCB. Move Ethernet, uSD, power switch and memory to the side. Fix broken traces
2022-09-06 Fix MicroSD_1140084168 symbol and footprint issue
2022-09-07 Silkscreen cleanup. Bump revision to 1.2.0
2022-09-08 Change PoE controller to TPS2373-4RGWR and update placement on PCB
2022-09-09 Finish layout with new PoE controller. DRC and silks clearing
2022-09-09 Loclib
2022-09-12 Update DFN3538 3D model
2022-09-14 Replace PoE IC to TPS2372-3RGWR with improved footprint
2022-09-14 Added PCIe sheet, initial connection of the PCIe interface
2022-09-19 For PCIe: added MGTAVTT calibration resistor, proper HCSL temination, REFCLK AC decoupling, PERST connection, corrected PRSNT1 to PRSNT2 connection.
2022-09-20 Add power monitors IC to the schematic
2022-09-21 Change shunt resistors to 10mOhm on VPP, VTT, 5V0, 3V3, 1V8 and 1V0 rails
2022-09-21 Added VTT_CNTL and SLP_S4 FPGA Control for Hot Swap
2022-09-22 Added hot-swap: button, LED indication, detection on ground pin. Updated SN74LVC1G07 symbol
2022-09-23 B2B FMC HPC connector added, recconected PCIe to new connector, added ETH mux
2022-09-26 Add power cycling circuitry
2022-09-26 Connect ETH mux, connect AUX_JTAG to FMC connector, add RC filter for HOT_SWAP_BUTTON signal
2022-09-27 Replaced JTAG to surface mount, Update FMC HPC socket
2022-09-27 Reconnect FMC signals to new socket, and JTAG to new connector
2022-09-28 Replace MODE2 jumpers with SMD DIP switch. Replace power cycle,VTT_CNTL and SLP_S4 ccircuits with tri-state buffer ones. Add possibilty to swith ETH paths with FPGA
2022-09-29 Re-add mounting holes, add tri-state buffer for FPGA_POWER_CYCLE signal
2022-09-30 Correct PCIe pin assigment, replace MODE2 symbol, export changes to PCB, progess in the new components placement
2022-10-03 All components inside the board area, fix FMC column B shift on schematic, add PCIe layer dependent rules
2022-10-05 Finish initial routing of PCIe
2022-10-06 Deskew PCIe, add bank 115,116 decoupling
2022-10-06 Increase PoE clereance, reroute SD card interface
2022-10-07 Add PoE labels for netclass assigment
2022-10-07 Propose optimized DDR4 pinout for die[6..9], initial BGA fanout for bank 32
2022-10-10 Update FPGA symbol (die to pad length), initial fanout for die [1..4]
2022-10-11 Add new pinout for bank 32 and 34, create custom DRC rules for DDR, initial routing for die 6,7,9
2022-10-12 Progress in DDR routing
2022-10-13 Finish assigning address, command and control pins. Finish initial rerouting of DDR4 interface
2022-10-14 optimize addres, clock, command lanes
2022-10-14 Optimize FPGA fanout for DDR4 interface
2022-10-17 Finish assigment and routing of ECC die
2022-10-17 Route internal end external (FMC) ETH interface, add additional VDDQ and ETH MUX decoupling
2022-10-18 Add ETH MUX passthrough, reroute HDMI to 100 Ohm differential, begin routing current measurment circuit
2022-10-19 Add kelvin connection to shunt resistors, move some data, control and address traces from layer In.9 to In.5, route current measurment circuit
2022-10-20 Route power cycle circuitry
2022-10-21 Implement LED and PB mechanical concept. Assign bank 15 to FMC, remove buttons and add new ones
2022-10-24 Improve mechanical concept
2022-10-25 Finish mechanical concept, add active capacitor discharge circuit for all AP DC-DC, add pushbutton controler circuit
2022-10-25 Fix BZX84C5V1-TP footprint assigment
2022-10-26 Assign and fanout on FPGA and FMC for bank 15 signals
2022-10-27 Progress in FMC routing
2022-10-28 Finish routing FMC, start routing remainig misc signals
2022-10-31 Route AUX JTAG to FMC connector
2022-10-31 Cleanup schematic
2022-10-31 Replace visualisation in README and schematic
2022-10-31 Update PDF schematic
2022-11-02 Add missing FMC vias, route: MODE, JTAG, active discharge, reconnect 5V buses
2022-11-03 Assign and connect misc. signals. Add, place and route decoupling capacitors
2022-11-04 Draw power supply polygons
2022-11-07 Finish power supply polygons, improve connector shield to ground connection
2022-11-07 Finish routing all connections
2022-11-08 Start length matching
2022-11-08 Length match and deskew Die 7, Die3, command, control and addres. Modify SPI Flash footprint
2022-11-09 Length match and deskew Die 4, Die 6, Die 8
2022-11-09 Minor readability improvements
2022-11-09 Length match and deskew Die 2
2022-11-09 Start matching and deskew Die 9
2022-11-09 Readability improvements
2022-11-09 replace 120R VRN, VRP resistors with 80.6R ones
2022-11-09 Finish DDR interface matching
2022-11-10 Match ECC die, deskew PCIe, signal integrity improvments
2022-11-10 Reduce FTDI termal vias
2022-11-14 Progress in HS matching and deskewing, clear DRC, implement schematic review changes, SI improvments
2022-11-15 SI improvments
2022-11-16 Improve PCIe SI, Lengt match FMC spare signals on layer In7
2022-11-17 Finish HS signals length matching and deskewing, provide copper balance
2022-11-18 Final touches
2022-11-21 Add remarks after review to the schenatic
2022-11-22 Fix the remark
2022-11-22 DDR SI improvments, optimize bom, apply review issues fix
2022-11-23 Optimize BOM, add all bank 115 and 116 REFCLK's to FMC connector
2022-11-25 Implement all review fixes, route control signals from FMC to FPGA
2022-11-25 Implement changes after gerber level review
2022-11-28 Fix SD card reference plane, minor polygon adjustment, fix PoE clereance, fix net class assigment
2022-11-28 GND plane cutout aligment
2022-11-28 Adjust 1V8_SYS plane
2022-11-28 Fix netclass assigment for impedance map generation
2022-12-01 Silkscreen adjustment, add PCB SHA, add missing 3D models
2022-12-02 Fix hidden silkscreen
2022-12-02 Add 1V2 rail power measurment
2022-12-02 Update PCB date code
2022-12-02 Fix missing netclass settings
2022-12-07 Restore outer layers via pads
2023-02-07 README: Update photo
2023-02-07 README: minor fixes
2023-03-24 Add Block diagram, update readme
2023-03-24 README: Update naming convention
2023-03-24 Add missing ON/OFF controller pull-ups, add possibility for instant turn off
2023-03-24 Change R208 vaule to 10k
2023-03-24 Remove U13 AUTCLS to GNDD connection
2023-03-24 Use ETH mux passthrough as default option, add LED passthrough
2023-03-24 Change R123 to 10k
2023-03-24 Apply fixes to PCB
2023-03-24 Bump revision and date on PCB
2023-03-24 Loclib of the project
2023-03-24 Add updated visualisation, fix date
2023-03-27 Update PCB naming
2023-03-27 Fix FPGA footprint
2023-03-27 Exclude virtual components from bom
2023-03-27 Update BSS138PW lib name and MPN
2023-03-30 README: update the license string
2023-04-08 README: fix rowhammer-tester links
2023-10-13 Cleanup
2023-10-13 Introduce component standardization
2023-10-16 Add OHP assets
2024-02-20 [#55119] component update

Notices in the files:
parts and their libraries:
Copyright 2016 Accelerated Designs. All rights reserved.
